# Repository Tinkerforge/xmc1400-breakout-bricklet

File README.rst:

XMC1400 Breakout Bricklet
=========================

This repository contains the firmware source code and the hardware design
files. The documentation generator configs can be found at
https://github.com/Tinkerforge/generators

Repository Content
------------------

software/:
 * examples/: Examples for all supported languages
 * build/: Compiled files
 * src/: Source code of firmware
 * Makefile: Makefile to build project

hardware/:
 * Contains KiCad project files and additionally schematics as PDF

datasheets/:
 * Contains datasheets for sensors and complex ICs that are used

Hardware
--------

The hardware is designed with the open source EDA Suite KiCad
(http://www.kicad.org). Before you are able to open the files,
you have to install the Tinkerforge kicad-libraries
(https://github.com/Tinkerforge/kicad-libraries). You can either clone
them directly in hardware/ or clone them in a separate folder and
symlink them into hardware/
(ln -s kicad_path/kicad-libraries project_path/hardware). After that you
can open the .pro file in hardware/ with KiCad and from there view and
modify the schematics and the PCB layout.

Software
--------

If you want to do your own Brick/Bricklet firmware development we highly
recommend that you use our build environment setup script and read the
tutorial (https://www.tinkerforge.com/en/doc/Tutorials/Tutorial_Build_Environment/Tutorial.html).

To compile the C code we recommend you to install the newest GNU Arm Embedded
Toolchain (https://launchpad.net/gcc-arm-embedded/+download).
You also need to install bricklib2 (https://github.com/Tinkerforge/bricklib2).

You can either clone it directly in software/src/ or clone it in a
separate folder and symlink it into software/src/
(ln -s bricklib_path/bricklib2 project_path/software/src/). Finally make sure to
have CMake installed (http://www.cmake.org/cmake/resources/software.html).

After that you can build the firmware by invoking make in software/.
The firmware (.zbin) can then be found in software/build/ and uploaded
with brickv (click button "Flashing" on start screen).

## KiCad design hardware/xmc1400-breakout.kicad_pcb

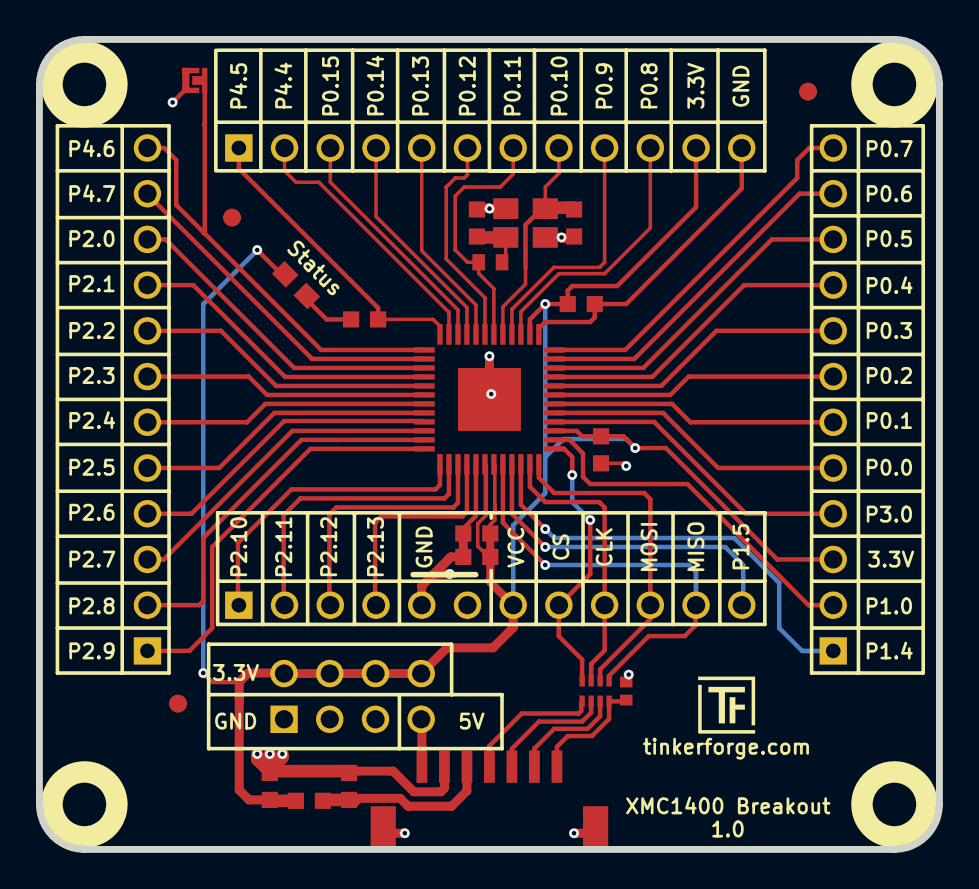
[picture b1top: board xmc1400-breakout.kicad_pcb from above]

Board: 2 copper layers, 50.0 x 45.0 mm, 32 parts (0 on the bottom side), 52 nets.

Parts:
C1, C2: 1uF; C0603F
C3, C4, C5: 100nF; C0603F
C6: 220nF; C0603F
C7: 220pF; C0402F
C8, C9: 10pF; C0603F
D3: blue; D0603E
FB1: FILTER; C0603F
Fiducial_Mark: VAL**; Fiducial_Mark
Fiducial_Mark#2, Fiducial_Mark#3: VAL**; Fiducial_Mark
P1: CON-SENSOR2
P2: BOOT; SolderJumper
P3, P4, P5, P6: CONN_01X12; pin_array_12
P7: CONN_02X04; pin_array_4x2
R1: 1k; R0603F
R9: DNP; R0402E
RP1: 82; 4X0402
U1: XMC1404; QFN48-EP2
U2, U3, U4, U5: DRILL; DRILL_NP
VAL: CE_5mm
VAL#2: WEEE_7mm
X1: 16MHz; CRYSTAL_3225

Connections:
+5V: P1.1, P7.7
GND: C1.1, C2.1, C3.2, C4.2, C5.2, C6.2, C7.2, C8.2, C9.2, P1.2, P1.EP, P2.1, P3.12, P5.5, P5.6, P7.1, P7.3, P7.5, U1.17, U1.37, U1.EP, X1.3
unnamed: C1.2, FB1.2, P1.3
unnamed: C7.1, P1.7, RP1.4
unnamed: C9.1, R9.2, X1.1
unnamed: D3.2, R1.2
unnamed: P1.4, RP1.1
unnamed: P1.5, RP1.2
unnamed: P1.6, RP1.3
Pin1: P2.2, P4.12, U1.1
Pin2: P4.11, U1.2
Pin3: P4.10, U1.3
Pin4: P4.9, U1.4
Pin5: P4.8, U1.5
Pin6: P4.7, U1.6
Pin7: P4.6, U1.7
Pin8: P4.5, U1.8
Pin9: P4.4, U1.9
Pin10: P4.3, U1.10
Pin11: P4.2, U1.11
Pin12: P4.1, U1.12
Pin13: P5.1, U1.13
Pin14: P5.2, U1.14
Pin15: P5.3, U1.15
Pin16: P5.4, U1.16
Pin21: P5.12, U1.21
Pin22: P6.1, U1.22
Pin26: P6.2, U1.26
Pin28: P6.4, U1.28
Pin29: P6.5, U1.29
Pin30: P6.6, U1.30
Pin31: P6.7, U1.31
Pin32: P6.8, U1.32
Pin33: P6.9, U1.33
Pin34: P6.10, U1.34
Pin35: P6.11, U1.35
Pin36: P6.12, U1.36
Pin39: P3.10, U1.39
Pin40: P3.9, U1.40
Pin41: C8.1, P3.8, U1.41, X1.2
Pin42: P3.7, R9.1, U1.42
Pin43: P3.6, U1.43
Pin44: P3.5, U1.44
Pin45: P3.4, U1.45
Pin46: P3.3, U1.46
Pin47: P3.2, U1.47
Pin48: P3.1, R1.1, U1.48
S-CLK: P5.9, RP1.7, U1.23
S-CS: P5.8, RP1.8, U1.25
S-MISO: P5.11, RP1.5, U1.20
S-MOSI: P5.10, RP1.6, U1.24
VCC: C2.2, C3.1, C4.1, C5.1, C6.1, D3.1, FB1.1, P3.11, P5.7, P6.3, P7.2, P7.4, P7.6, P7.8, U1.18, U1.19, U1.27, U1.38

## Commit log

2017-02-07 initial check in
2017-02-07 Adding current unfinished version
2017-02-07 Add VCC connections
2017-02-07 removing rescue lib
2017-02-07 Optical improvements
2017-02-07 Add pin markings
2017-02-07 Fix fiducial mark position top left
2017-03-27 Add stub software for XMC1400 breakout
2017-08-29 Add 3d information
2017-08-29 Add more headers (GND, VCC, 5V)
2017-09-14 Fix typo
2017-09-14 Fix conductor path connection
2017-10-13 Add missing bootstrapper configuration
2018-03-05 Remove unused flash-size define
2019-02-07 name change and added sym lib table
2019-02-07 added text on back silkscreen
2019-02-07 added filter resitor and cap in dataline
2019-03-19 Use new docker-enabled Makefile
2019-03-19 Use relative path to kicad-libraries
2019-03-20 Add example firmware for XMC1400 Breakout Bricklet
2019-04-03 Enable post calibration
2019-05-03 Add auto-generated examples
2019-05-15 fix file names
2019-06-12 specify processor
2019-06-13 specify resistor
2019-06-13 fix connector properties
2019-08-14 Add changelog entry for inital version
2019-08-15 add 3d data
2019-08-15 Turn external oscillator off (by default)
    Can be enabled by the user if needed
2019-08-15 Fix input hysteresis check
2019-08-15 Fix rev of v2.0.0
2019-08-15 fix filename
2019-08-15 fix schematic symbols, add pdf
2019-08-22 rust: Style cleanup
2019-08-22 Remove development marker
2020-01-13 examples: Use python3 input instead of python2 raw_input.
2020-01-13 examples: mqtt: Remove trailing whitespace.
2020-03-16 Whitespace
2020-03-23 mqtt: Update for loop style
2020-04-07 examples: rust: Always block when calling bindings functions.
2020-08-19 Add uc examples.
2020-08-25 uc: Fix whitespace
2020-08-27 uc: Fix warnings.
2020-09-02 uc: Add example driver note.
2021-10-25 Update KiCad link
    https://www.kicad.org/blog/2021/10/Avoid-links-to-former-kicad-domain/
2022-04-19 examples: uc: Rename TF_HalContext to TF_HAL.
2022-04-27 uc: Adapt to bindings changes
2022-07-06 Add license files.
2025-10-04 Fix compatibility with new Docker build image (GCC 14.2.1)

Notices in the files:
hardware/xmc1400-breakout.kicad_pcb:
Licensed under CERN OHL v.1.1
Copyright (©) 2017, B.Nordmeyer
Copyright Tinkerforge GmbH 2015.
This documentation describes Open Hardware and is licensed under the
CERN OHL v. 1.1.
